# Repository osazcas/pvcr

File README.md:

View this project on [CADLAB.io](https://cadlab.io/project/28424). 

# pvcr

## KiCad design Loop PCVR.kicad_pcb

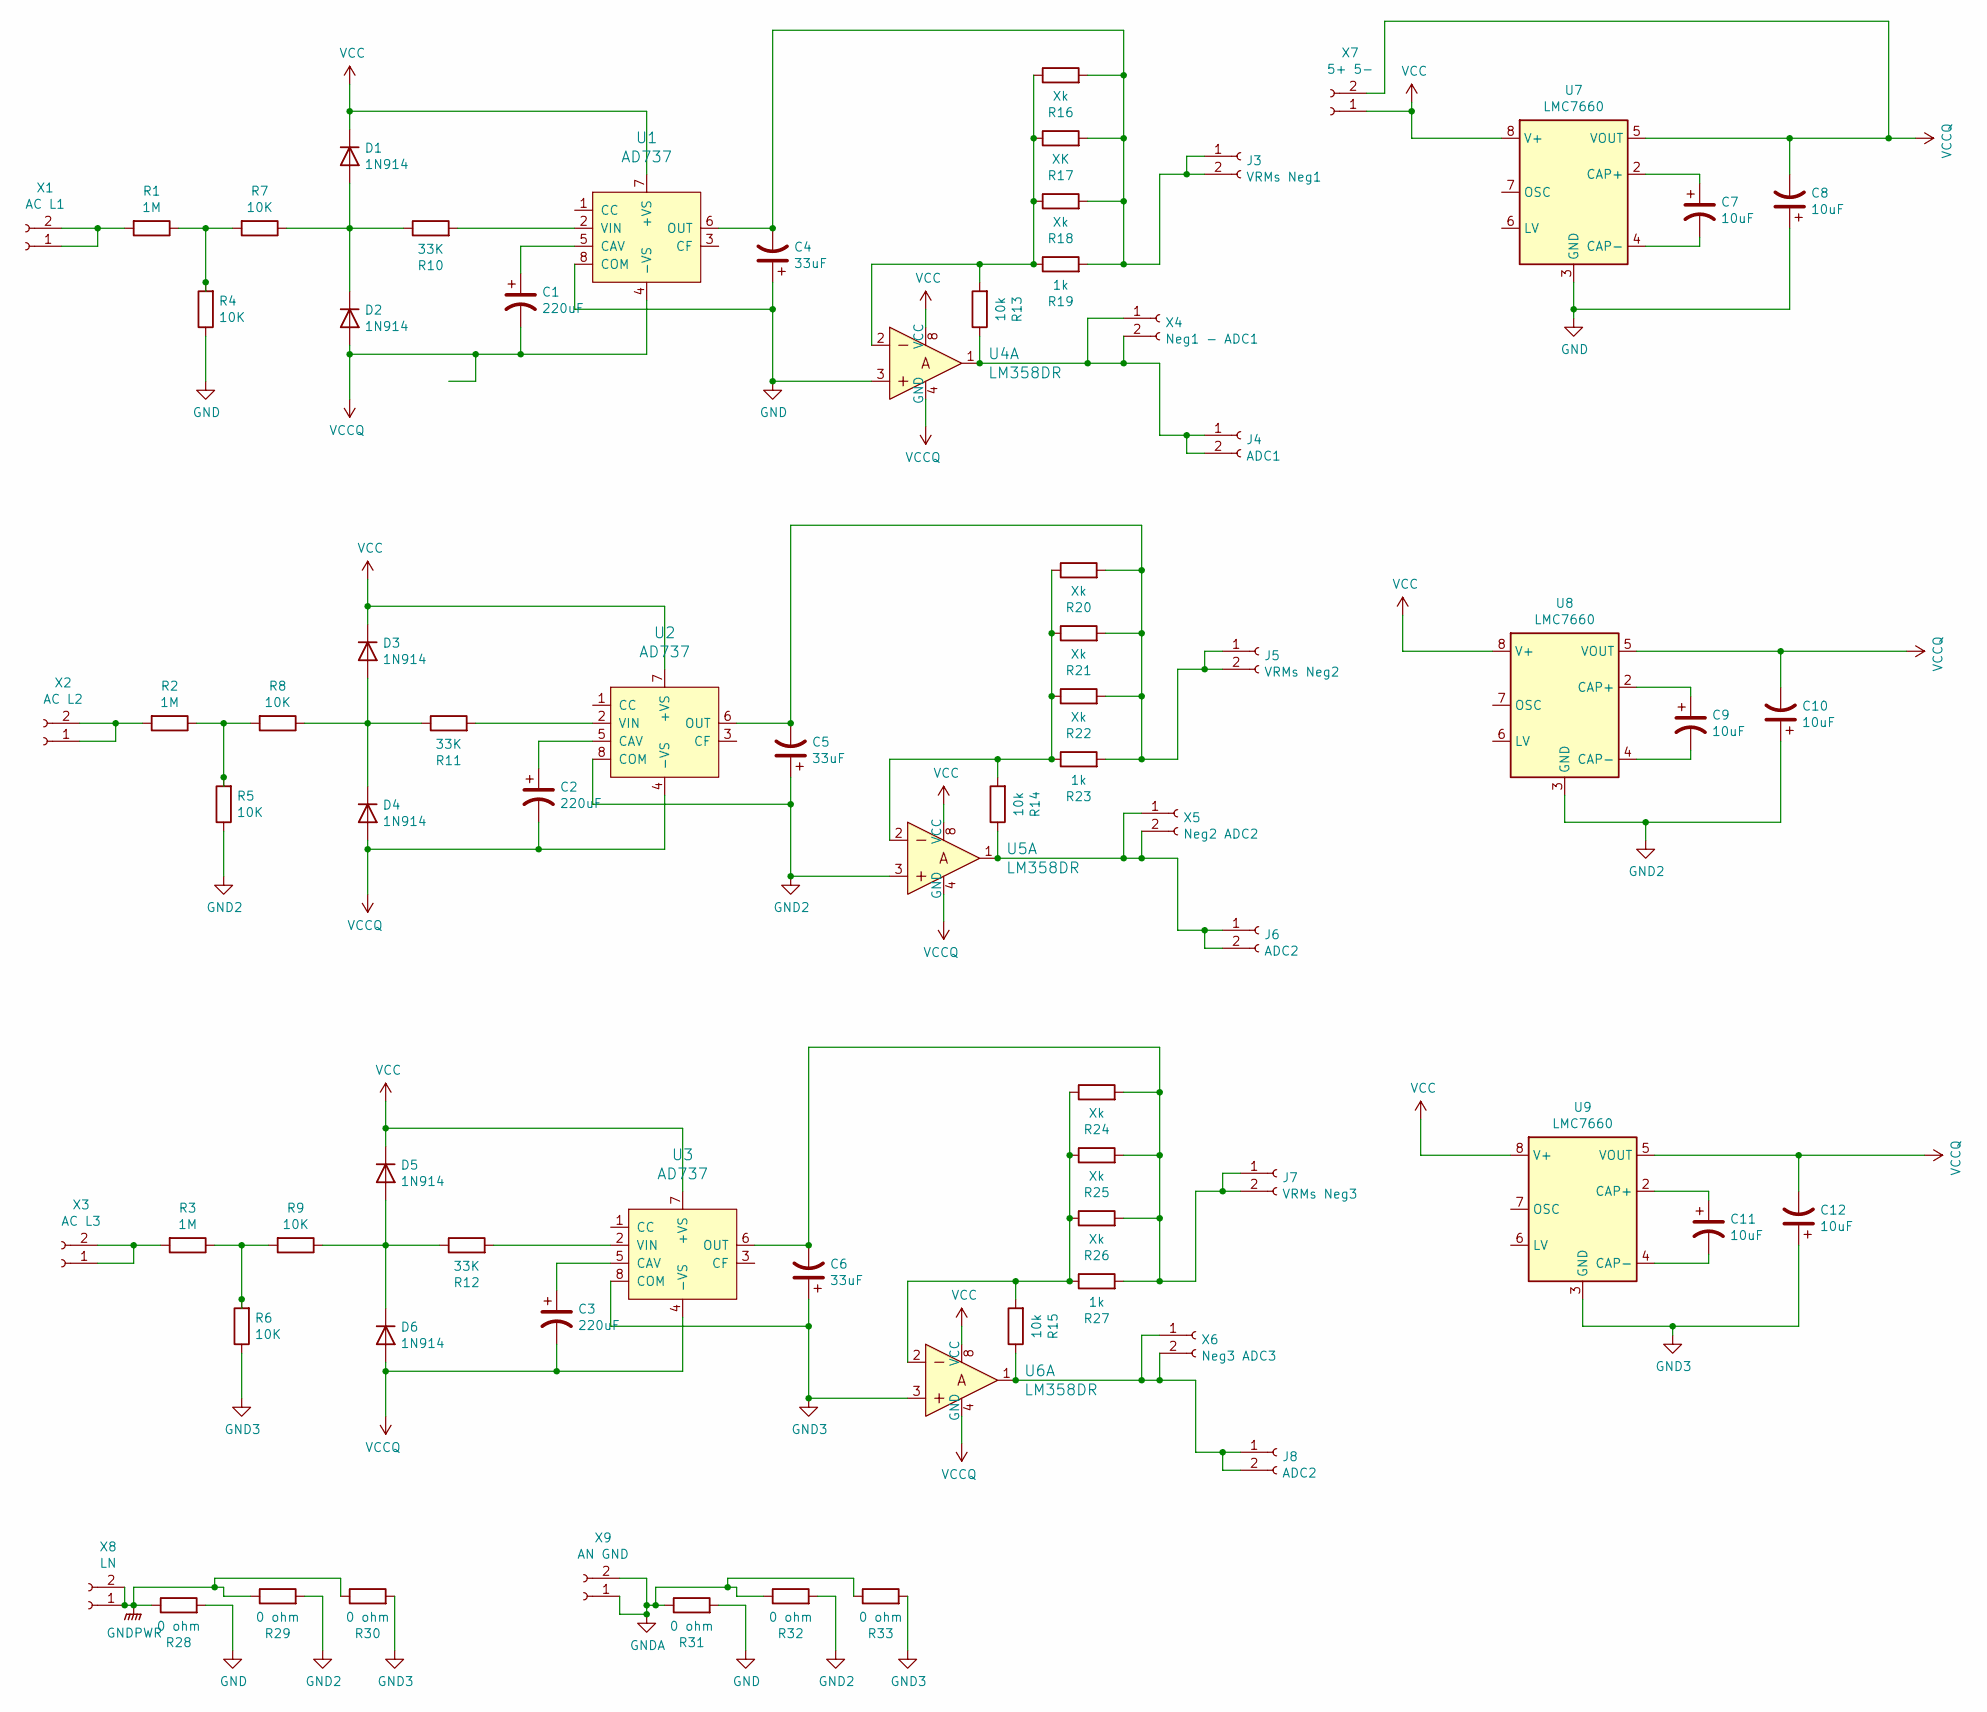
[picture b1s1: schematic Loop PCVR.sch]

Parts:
C1, C2, C3: 220uF; CP_Radial_D10.0mm_P5.00mm
C4, C5, C6: 33uF; CP_Radial_D5.0mm_P2.00mm
C7, C8, C9, C10, C11, C12: 10uF; CP_Radial_D5.0mm_P2.00mm
D1, D2, D3, D4, D5, D6: 1N914; D_DO-35_SOD27_P7.62mm_Horizontal
J3: VRMs Neg1; PinHeader_1x02_P2.54mm_Vertical
J4: ADC1; PinHeader_1x02_P2.54mm_Vertical
J5: VRMs Neg2; PinHeader_1x02_P2.54mm_Vertical
J6, J8: ADC2; PinHeader_1x02_P2.54mm_Vertical
J7: VRMs Neg3; PinHeader_1x02_P2.54mm_Vertical
R1, R2, R3: 1M; R_1210_3225Metric_Pad1.42x2.65mm_HandSolder
R4, R5, R6, R7, R8, R9: 10K; R_1210_3225Metric_Pad1.42x2.65mm_HandSolder
R10, R11, R12: 33K; R_1210_3225Metric_Pad1.42x2.65mm_HandSolder
R13, R14, R15: 10k; R_1210_3225Metric_Pad1.42x2.65mm_HandSolder
R16, R18, R20, R21, R22, R24, R25, R26: Xk; R_1210_3225Metric_Pad1.42x2.65mm_HandSolder
R17: XK; R_1210_3225Metric_Pad1.42x2.65mm_HandSolder
R19, R23, R27: 1k; R_1210_3225Metric_Pad1.42x2.65mm_HandSolder
R28, R29, R30, R31, R32, R33: 0 ohm; R_1210_3225Metric_Pad1.42x2.65mm_HandSolder
U1, U2, U3: AD737; SOIC-8_3.9x4.9mm_P1.27mm; MPN AD736JNZ; Digi-Key_PN AD736JNZ-ND
U4, U5, U6: LM358DR; SOIC-8_3.9x4.9mm_P1.27mm; MPN LM358DR; Digi-Key_PN 296-1014-1-ND
U7, U8, U9: LMC7660; SOIC-8_3.9x4.9mm_P1.27mm
X1: AC L1; TerminalBlock_MetzConnect_Type055_RT01502HDWU_1x02_P5.00mm_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
X2: AC L2; TerminalBlock_MetzConnect_Type055_RT01502HDWU_1x02_P5.00mm_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
X3: AC L3; TerminalBlock_MetzConnect_Type055_RT01502HDWU_1x02_P5.00mm_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
X4: Neg1 - ADC1; TerminalBlock_MetzConnect_Type055_RT01502HDWU_1x02_P5.00mm_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
X5: Neg2 ADC2; TerminalBlock_MetzConnect_Type055_RT01502HDWU_1x02_P5.00mm_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
X6: Neg3 ADC3; TerminalBlock_MetzConnect_Type055_RT01502HDWU_1x02_P5.00mm_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
X7: 5+ 5-; TerminalBlock_MetzConnect_Type055_RT01502HDWU_1x02_P5.00mm_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
X8: LN; TerminalBlock_MetzConnect_Type055_RT01502HDWU_1x02_P5.00mm_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
X9: AN GND; TerminalBlock_MetzConnect_Type055_RT01502HDWU_1x02_P5.00mm_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

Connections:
GND: C4.1, C8.1, R4.1, R28.2, R31.2, U1.8 (COM), U4.3, U7.3 (GND)
GND2: C5.1, C10.1, R5.1, R29.2, R32.2, U2.8 (COM), U5.3, U8.3 (GND)
GND3: C6.1, C12.1, R6.1, R30.2, R33.2, U3.8 (COM), U6.3, U9.3 (GND)
GNDA: R31.1, R32.1, R33.1, X9.1, X9.2
GNDPWR: R28.1, R29.1, R30.1, X8.1, X8.2
unnamed: C1.1, U1.5 (CAV)
unnamed: C2.1, U2.5 (CAV)
unnamed: C3.1, U3.5 (CAV)
unnamed: C4.2, J3.1, J3.2, R16.2, R17.2, R18.2, R19.2, U1.6 (OUT)
unnamed: C5.2, J5.1, J5.2, R20.2, R21.2, R22.2, R23.2, U2.6 (OUT)
unnamed: C6.2, J7.1, J7.2, R24.2, R25.2, R26.2, R27.2, U3.6 (OUT)
unnamed: C7.1, U7.2 (CAP+)
unnamed: C7.2, U7.4 (CAP-)
unnamed: C9.1, U8.2 (CAP+)
unnamed: C9.2, U8.4 (CAP-)
unnamed: C11.1, U9.2 (CAP+)
unnamed: C11.2, U9.4 (CAP-)
unnamed: D1.2 (A), D2.1 (K), R7.1, R10.1
unnamed: D3.2 (A), D4.1 (K), R8.1, R11.1
unnamed: D5.2 (A), D6.1 (K), R9.1, R12.1
unnamed: J4.1, J4.2, R13.1, U4.1, X4.1, X4.2
unnamed: J6.1, J6.2, R14.1, U5.1, X5.1, X5.2
unnamed: J8.1, J8.2, R15.1, U6.1, X6.1, X6.2
unnamed: R1.1, R4.2, R7.2
unnamed: R1.2, X1.1, X1.2
unnamed: R2.1, R5.2, R8.2
unnamed: R2.2, X2.1, X2.2
unnamed: R3.1, R6.2, R9.2
unnamed: R3.2, X3.1, X3.2
unnamed: R10.2, U1.2 (VIN)
unnamed: R11.2, U2.2 (VIN)
unnamed: R12.2, U3.2 (VIN)
unnamed: R13.2, R16.1, R17.1, R18.1, R19.1, U4.2
unnamed: R14.2, R20.1, R21.1, R22.1, R23.1, U5.2
unnamed: R15.2, R24.1, R25.1, R26.1, R27.1, U6.2
VCC: D1.1 (K), D3.1 (K), D5.1 (K), U1.7 (+VS), U2.7 (+VS), U3.7 (+VS), U4.8 (VCC), U5.8 (VCC), U6.8 (VCC), U7.8 (V+), U8.8 (V+), U9.8 (V+), X7.1
VCCQ: C1.2, C2.2, C3.2, C8.2, C10.2, C12.2, D2.2 (A), D4.2 (A), D6.2 (A), U1.4 (-VS), U2.4 (-VS), U3.4 (-VS), U4.4 (GND), U5.4 (GND), U6.4 (GND), U7.5 (VOUT), U8.5 (VOUT), U9.5 (VOUT), X7.2

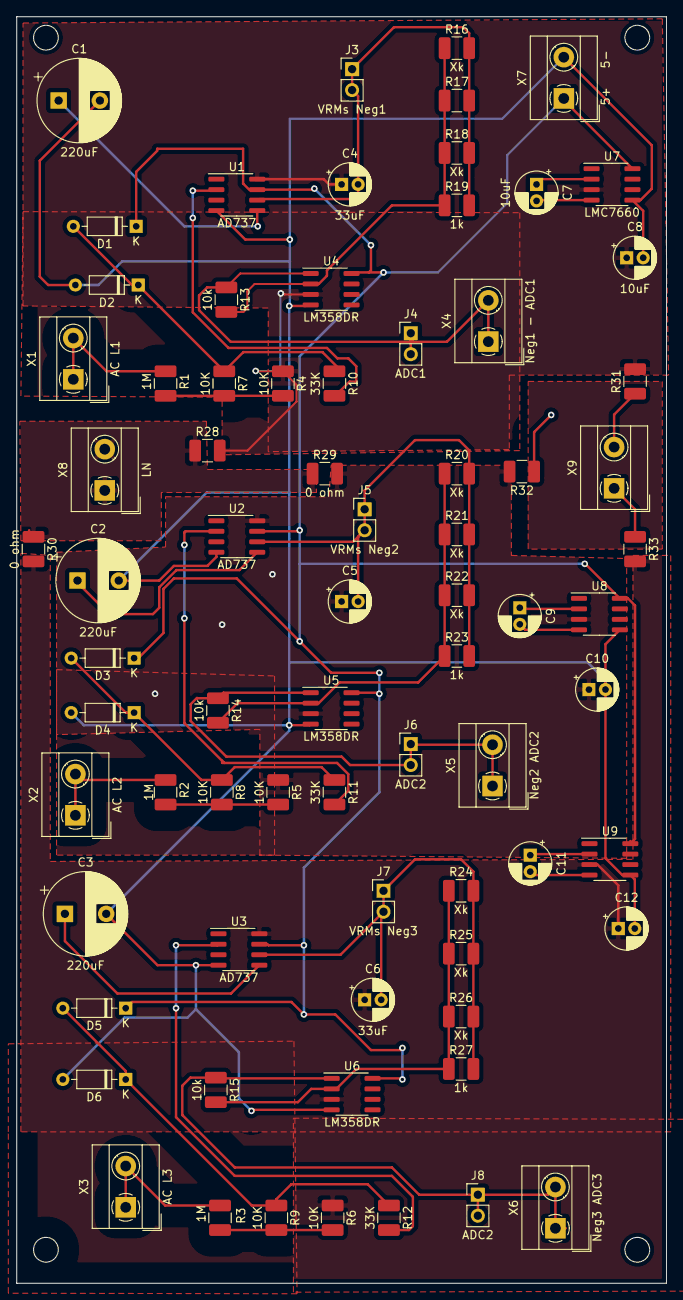
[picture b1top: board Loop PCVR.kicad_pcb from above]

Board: 2 copper layers, 78.7 x 153.5 mm, 75 parts (0 on the bottom side), 37 nets.

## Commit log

2024-09-08 Backlink to CADLAB.io has been added.
